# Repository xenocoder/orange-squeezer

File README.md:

Orange Squeezer compresor. Not yet done

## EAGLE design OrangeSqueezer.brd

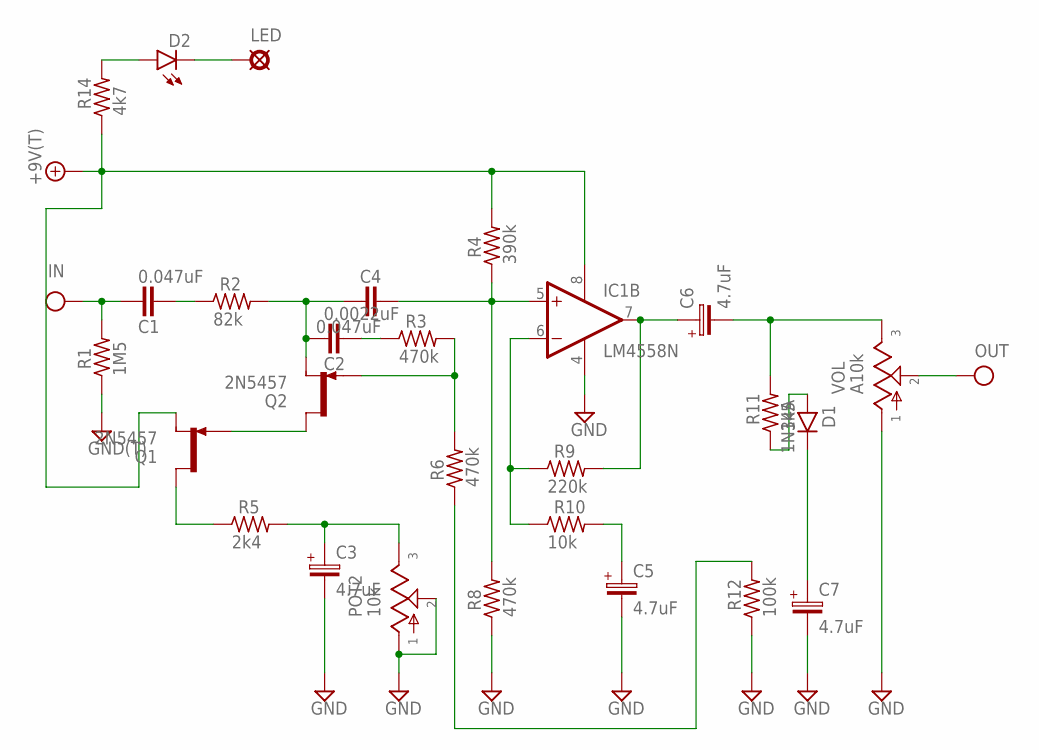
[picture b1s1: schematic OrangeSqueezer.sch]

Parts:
+9V: +9V(T); SQUARE
C1, C4: 0.047uF; 072X025
C2: 0.0022uF; 072X025
C3, C5, C6, C7: 4.7uF; 050_020_1
D1: 1N34A; DO41-3
D2: LED3MM
G: GND(T); SQUARE
IC1: LM4558N; DIL08
IN: IN(T); SQUARE
LED: LED; SQUARE
OUT: OUT(T); SQUARE
POT2: 10k; B25P
Q1, Q2: 2N5457; TO92-
R1: 1M5; R0207/3
R2: 82k; R0207/3
R3, R6, R8: 470k; R0207/3
R4: 390k; R0207/3
R5: 2k4; R0207/3
R9: 220k; R0207/3
R10: 10k; R0207/3
R11: 1k5; R0207/3
R12: 100k; R0207/3
R14: 4k7; R0207/3
VOL: A10k; 16MM_PCB_PADS

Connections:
+9V: +9V.1, IC1.8 (V+), Q1.2 (S), R4.2, R14.1
GND: C3.-, C5.-, C7.-, G.1, IC1.4 (V-), POT2.1, POT2.2, R1.1, R8.1, R12.1, VOL.1
IN: C1.2, IN.1, R1.2
unnamed: C1.1, R2.1
unnamed: Q1.3 (D), R5.1
unnamed: Q1.1 (G), Q2.3 (D)
unnamed: IC1.6 (-IN), R9.1, R10.1
unnamed: C2.2, C4.1, Q2.2 (S), R2.2
unnamed: C2.1, R3.1
unnamed: Q2.1 (G), R3.2, R6.2
unnamed: C3.+, POT2.3, R5.2
unnamed: C4.2, IC1.5 (+IN), R4.1, R8.2
unnamed: C5.+, R10.2
unnamed: C6.-, R11.2, VOL.3
unnamed: D1.A, R11.1
unnamed: C7.+, D1.C
unnamed: D2.A, R14.2
unnamed: D2.K (C), LED.1
unnamed: R6.1, R12.2
unnamed: C6.+, IC1.7 (OUT), R9.2
OUT: OUT.1, VOL.2

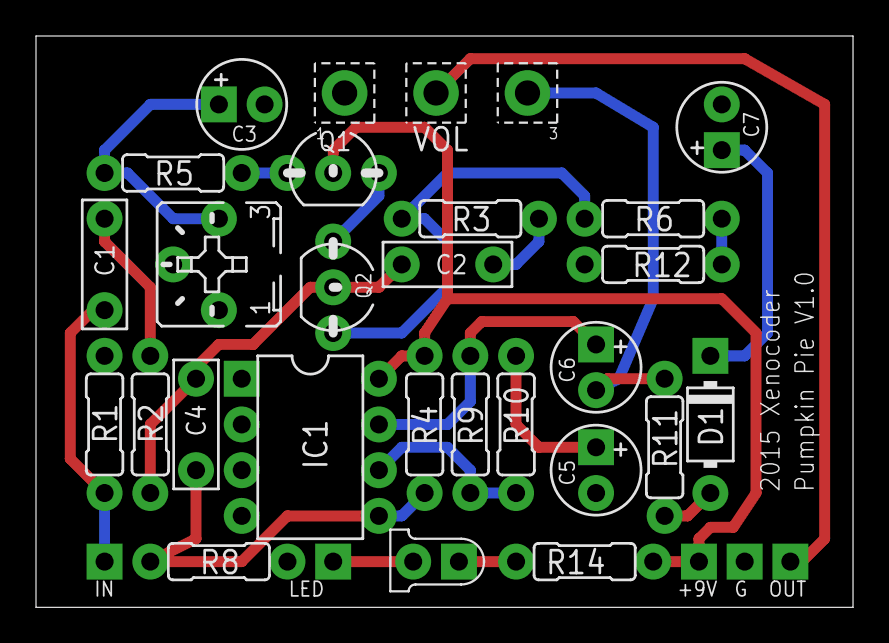
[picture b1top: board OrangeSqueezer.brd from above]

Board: 2 copper layers, 45.4 x 31.7 mm, 31 parts (0 on the bottom side), 21 nets.

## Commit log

2015-12-26 Version 1.0 of Pumpkin Pie sent to Oshpark 12/26/15
2020-03-08 Added Partlist and PCB
2020-04-29 First commit for The Thing tremolo
2020-05-17 Uploaded new files for Asami Compressor (Orange Squeezer)
